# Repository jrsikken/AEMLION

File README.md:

# AEMLION
This AEMLION is a 0.8x0.6 inch (20x15mm) PCB with the AEM10941 Solar Harvesting IC from E-peas. It efficiently converts solar energy into Li-ion battery charge, it even works with indoor light. It features 3.3V and 1.8V regulated outputs that are enabled when the battery has useful charge and a low battery warning that informs the user of impending shutdown when the battery runs low. It easily integrates into other projects because of small size, castellated via's, and when soldered onto 0.1" pitch header it fits in a breadboard.

I sell this board on Tindie. https://www.tindie.com/products/14711/

This project is on Hackaday https://hackaday.io/project/160376/

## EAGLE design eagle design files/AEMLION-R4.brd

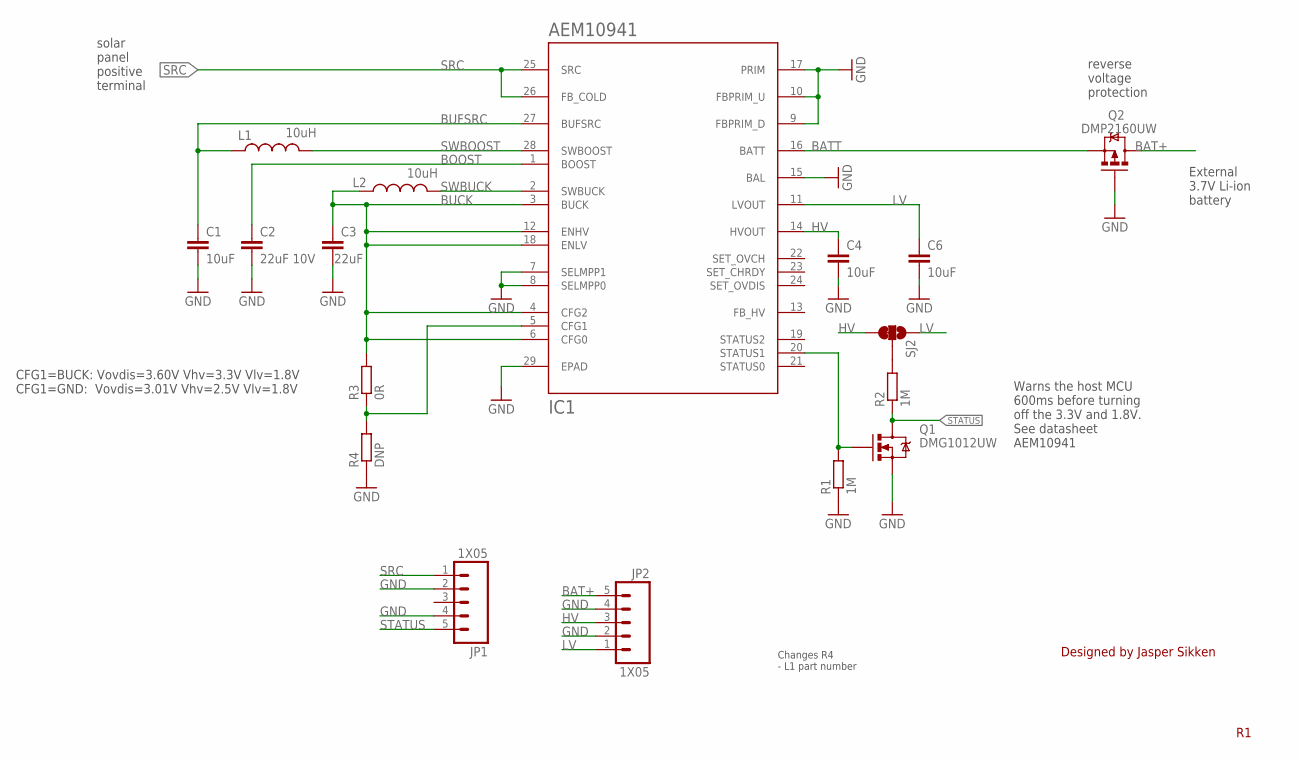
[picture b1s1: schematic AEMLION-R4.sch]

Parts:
C1, C4, C6: 10uF; C0603; MPN 1049P
C2: 22uF 10V; C0603; MPN CGA5L1X7S1A226M160AC
C3: 22uF; C0603; MPN 1049P
IC1: AEM10941; QFN50P505X505X90-28
JP1, JP2: 1X05; 1X05_2.54MM_ROUND_NOSILK
L1: 10uH; L_3225MM
L2: 10uH; L0603; MPN CK2125100M-T
Q1: DMG1012UW; SOT323
Q2: DMP2160UW; SOT323
R1, R2: 1M; R0402
R3: 0R; R0402
R4: DNP; R0402
SJ2: SOLDERJUMPER_3WAY_12SHORT3WAY; SJ_3S_NC_0402

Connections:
BAT+: JP2.5, Q2.3 (D)
BATT: IC1.16 (BATT), Q2.2 (S)
BOOST: C2.1, IC1.1 (BOOST)
BUCK: C3.1, IC1.3 (BUCK), IC1.4 (CFG2), IC1.6 (CFG0), IC1.12 (ENHV), IC1.18 (ENLV), L2.1, R3.2
BUFSRC: C1.1, IC1.27 (BUFSRC), L1.1
GND: C1.2, C2.2, C3.2, C4.2, C6.2, IC1.7 (SELMPP1), IC1.8 (SELMPP0), IC1.9 (FBPRIM_D), IC1.10 (FBPRIM_U), IC1.15 (BAL), IC1.17 (PRIM), IC1.29 (EPAD), JP1.2, JP1.4, JP2.2, JP2.4, Q1.2 (S), Q2.1 (G), R1.1, R4.1
HV: C4.1, IC1.14 (HVOUT), JP2.3, SJ2.1
LV: C6.1, IC1.11 (LVOUT), JP2.1, SJ2.3
unnamed: R2.2, SJ2.2
unnamed: IC1.5 (CFG1), R3.1, R4.2
SRC: IC1.25 (SRC), IC1.26 (FB_COLD), JP1.1
STATUS: JP1.5, Q1.3 (D), R2.1
STATUS1: IC1.20 (STATUS1), Q1.1 (G), R1.2
SWBOOST: IC1.28 (SWBOOST), L1.2
SWBUCK: IC1.2 (SWBUCK), L2.2

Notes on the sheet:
External 3.7V Li-ion battery
Warns the host MCU 600ms before turning off the 3.3V and 1.8V. See datasheet AEM10941
Designed by Jasper Sikken
solar panel positive terminal
reverse voltage protection
CFG1=BUCK: Vovdis=3.60V Vhv=3.3V Vlv=1.8V CFG1=GND: Vovdis=3.01V Vhv=2.5V Vlv=1.8V
Changes R4 - L1 part number

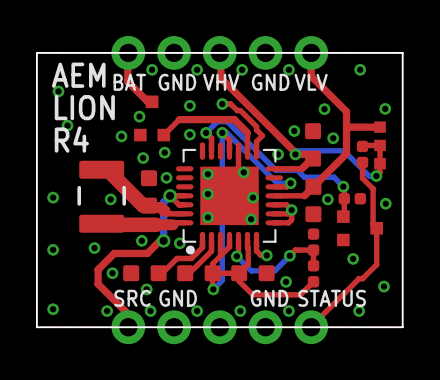
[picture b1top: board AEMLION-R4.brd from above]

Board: 2 copper layers, 20.3 x 15.2 mm, 17 parts (0 on the bottom side), 15 nets.

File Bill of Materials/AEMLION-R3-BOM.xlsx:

Reference | QTY | Value | Package | Manufacturer | Manufacturer Part number | Description | Voltage | Dielectric | Tolerance
C1,C3, C4, C6 | 4 | 10uF | C0603 | Generic part | Generic part | capacitor | 10V | X5R | 0.2
C2 | 1 | 22uF | C0603 | Generic part | Generic part | capacitor | 10V | X5R | 0.2
L1 | 1 | 10uH-0.55A | LPS4012 | COILCRAFT | LPS4012-103MRB | inductor
L2 | 1 | 10uH | L0603 | TDK | MLZ1608M100WT000 | inductor
Q2 | 1 | NTS2101PT1G | SOT323 | ON Semiconductor | NTS2101PT1G | mosfet
R1, R2 | 2 | 1M | R0402 | Generic part | Generic part | resistor
R3 | 1 | 0R | R0402 | Generic part | Generic part | resistor
Q1 | 1 | DMG1012UW-7 | SOT323 | Diodes | DMG1012UW-7 | mosfet
IC1 | 1 | AEM10941 | QFN50P505X50 | E-peas | AEM10941 | IC

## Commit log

2018-09-09 First release
2018-09-15 Update LICENSE
2018-11-09 added schematic in png format
2018-11-27 Revision 2B Reduced the paste under IC1 to 50% of the exposed pad
2019-02-16 Split a sentence
2019-05-28 specified L2 manufacturer and part number in Bill of Materials
